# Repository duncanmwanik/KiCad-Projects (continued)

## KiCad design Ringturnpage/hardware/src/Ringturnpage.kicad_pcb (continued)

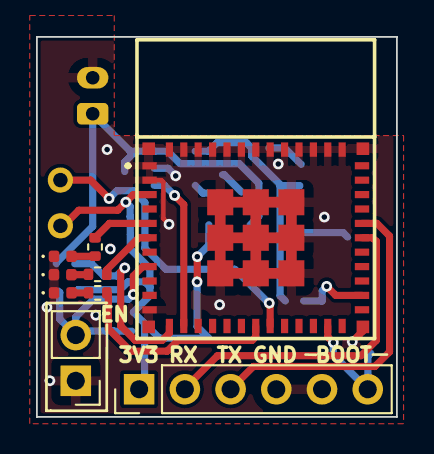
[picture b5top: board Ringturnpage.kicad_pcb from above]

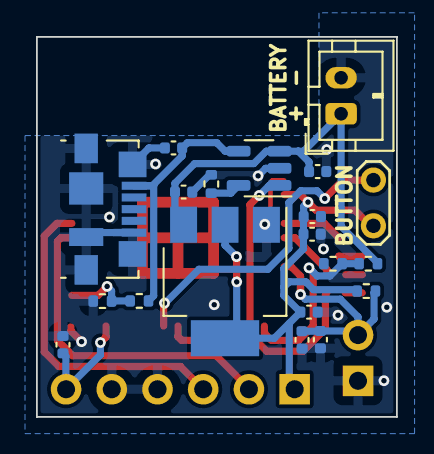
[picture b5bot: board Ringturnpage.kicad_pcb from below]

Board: 2 copper layers, 20.0 x 21.1 mm, 29 parts (20 on the bottom side), 19 nets.

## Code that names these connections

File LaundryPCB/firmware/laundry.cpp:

// ******* WASHING MACHINE CONTROLLER using WIFI
// Notifying control software about material left in the box not yet implemented
#include <Arduino.h>
#include <WiFi.h>
#include <HTTPClient.h>

const char* ssid = "WIFI_NAME";
const char* password = "WIFI_PASS";

const int START = 4;
const int STOP = 5;

// we use the solenoid taps rate of flow for each material and time
// to know what amount to dispense into the washing machine
const int WATER = 13;
const int HOT_WATER = 12;
const int BLEACH = 16;
const int POWDER = 14;
const int SOFTENER = 15;
const int BUZZER = 18;
const int WASHER = 18;
const int DRYER = 18;

// we use 
const int SENSOR_WATER = 2;
const int SENSOR_POWDER = 2;
const int SENSOR_BLEACH = 2;
const int SENSOR_SOFTENER = 2;

bool available = true;
bool start = false;

const char* get_order = "http://IP_ADDRESS_CONTROL_SOFTWARE/order";
const char* get_water = "http://IP_ADDRESS_CONTROL_SOFTWARE/water";
const char* get_hot_water = "http://IP_ADDRESS_CONTROL_SOFTWARE/hotwater";
const char* get_powder = "http://IP_ADDRESS_CONTROL_SOFTWARE/powder";
const char* get_bleach = "http://IP_ADDRESS_CONTROL_SOFTWARE/bleach";
const char* get_softener_size = "http://IP_ADDRESS_CONTROL_SOFTWARE/softener";
const char* get_start = "http://IP_ADDRESS_CONTROL_SOFTWARE/start";

String order = "none";
String hot_water_size;
String water_size;
String powder_size;
String bleach_size;
String softener_size;
String hot_water_size;
String start_str;

void setup() {

  pinMode(START, INPUT_PULLUP);
  pinMode(STOP, INPUT_PULLUP);
  pinMode(WATER, OUTPUT);
  pinMode(HOT_WATER, OUTPUT);
  pinMode(POWDER, OUTPUT);
  pinMode(BLEACH, OUTPUT);
  pinMode(SOFTENER, OUTPUT);
  pinMode(SENSOR_WATER, INPUT);
  pinMode(SENSOR_POWDER, INPUT);
  pinMode(SENSOR_BLEACH, INPUT);
  pinMode(SENSOR_SOFTENER, INPUT);

  WiFi.begin(ssid, password);
  while(WiFi.status() != WL_CONNECTED) { // turn LED on to show board is connected to WIFI
    delay(500);
    digitalWrite(GPIO_NUM_2, HIGH);
  }
}

void loop() {
  if(WiFi.status()== WL_CONNECTED){
    // if there is no order in progress
    if(order == "none"){
      order = httpGETRequest(get_order);
      hot_water_size = httpGETRequest(get_hot_water);
      water_size = httpGETRequest(get_water);
      powder_size = httpGETRequest(get_powder);
      bleach_size = httpGETRequest(get_bleach);
      softener_size = httpGETRequest(get_softener_size);
      
      // convert material values to int since these are time delay values
      int hot_water_value = hot_water_size.toInt();
      int water_value = water_size.toInt();
      int powder_value = powder_size.toInt();
      int bleach_value = bleach_size.toInt();
      int softener_value= softener_size.toInt();

      // if order is not empty, release material to the machine
      if(order != ""){
        // if the material value is 0, then that material won't be released
        // turn on each solenoid tap for the specified time period
        if(hot_water_value != 0){
          digitalWrite(HOT_WATER, HIGH);
          delay(hot_water_value);
          digitalWrite(HOT_WATER, LOW);
        }
        if(water_value != 0){
          digitalWrite(WATER, HIGH);
          delay(water_value);
          digitalWrite(WATER, LOW);
        }
        if(powder_value != 0){
          digitalWrite(POWDER, HIGH);
          delay(powder_value);
          digitalWrite(POWDER, LOW);
        }
        if(bleach_value != 0){
          digitalWrite(BLEACH, HIGH);
          delay(bleach_value);
          digitalWrite(BLEACH, LOW);
        }
        if(softener_value != 0){
          digitalWrite(SOFTENER, HIGH);
          delay(softener_value);
          digitalWrite(SOFTENER, LOW);
        }

      }
    }
    // if there is an order already in progress
    else{
      // get status value from control software
      start_str = httpGETRequest(get_start);
      // if START control button has been pressed
      if(digitalRead(START)){
        start_str = "1";
      }
      // if STOP control button has been pressed
      if(digitalRead(STOP)){
        start_str = "0";
      }
      // if 1, start washing process
      if(start_str=="1"){

        // DO WASHING PROCESS CODE

      }
      // if 0, stop washing process
      else if(start_str == "0"){
        
        // STOP WASHING PROCESS CODE

      }
      // if 2, cancel the order
      else if(start_str == "2"){

        order = "none";

      }

    }

  }
  else{ // flash LED on and off to show board has not connected to WIFI
    digitalWrite(GPIO_NUM_2, HIGH);
    delay(300);
    digitalWrite(GPIO_NUM_2, HIGH);
  }

}

String httpGETRequest(const char* serverName) {
  WiFiClient client;
  HTTPClient http;
    
  // Your Domain name with URL path or IP address with path
  http.begin(client, serverName);
  
  // Send HTTP POST request
  int httpResponseCode = http.GET();
  
  String payload = "--"; 
  
  if (httpResponseCode>0) {
    Serial.print("HTTP Response code: ");
    Serial.println(httpResponseCode);
    payload = http.getString();
  }
  else {
    Serial.print("Error code: ");
    Serial.println(httpResponseCode);
  }
  // Free resources
  http.end();

  return payload;
}

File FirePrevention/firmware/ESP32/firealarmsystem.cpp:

// ******* FIRE PREVENTION AND ALARM SYSTEM
#include <Arduino.h>
#include <WiFi.h>
#include <ESP_Mail_Client.h>
#include <HTTPClient.h>
#include <Firebase_ESP_Client.h>
#include "DHT.h"
#define DHTPIN 34 // Digital pin connected to the DHT sensor
#define DHTTYPE DHT22

//Provide the token generation process info.
#include "addons/TokenHelper.h"
//Provide the RTDB payload printing info and other helper functions.
#include "addons/RTDBHelper.h"

// Insert Firebase project API Key
#define API_KEY "FIREBASE_PROJECT_API_KEY"

// Insert RTDB URLefine the RTDB URL 
#define DATABASE_URL "FIREBASE_DATABASE_URL" 

// For the email service
#define SMTP_HOST "smtp.gmail.com"
#define SMTP_PORT 465
// The sign in credentials 
#define AUTHOR_EMAIL "mynamesgmail.com"
#define AUTHOR_PASSWORD "my_email_password"

// Recipient's email
#define RECIPIENT_EMAIL "receiveremail@gmail.com"

// The SMTP Session object used for Email sending 
SMTPSession smtp;

// Callback function to get the Email sending status 
void smtpCallback(SMTP_Status status);

//Define Firebase Data object
FirebaseData fbdo;

FirebaseAuth auth;
FirebaseConfig config;

bool signupOK = false;

// Temperature sensor instance
DHT dht(DHTPIN, DHTTYPE);

const char* ssid = "WIFI_NAME";
const char* password = "WIFI_PASS";

const int ALARM = 12;
const int GAS = 33;
const int FLAME = 32;

int counter = 0;  
static bool hasWifi = false;

//////////////
// Network //
////////////

static void InitWifi()
{
  Serial.println("Connecting...");
  WiFi.begin(ssid, password);
  while (WiFi.status() != WL_CONNECTED) {
    delay(500);
    Serial.print(".");
  }
  hasWifi = true;
  Serial.println("WiFi connected");
  Serial.println("IP address: ");
  Serial.println(WiFi.localIP());
}

void setup()
{
  Serial.begin(115200);
  pinMode(FLAME, INPUT);
  pinMode(GAS, INPUT);
  Serial.println("ESP32 Device");
  Serial.println("Initializing...");

    // Assign the api key (required) 
  config.api_key = API_KEY;

  // Assign the RTDB URL (required) 
  config.database_url = DATABASE_URL;

  // Sign up 
  if (Firebase.signUp(&config, &auth, "", "")){
    Serial.println("ok");
    signupOK = true;
  }
  else{
    Serial.printf("%s\n", config.signer.signupError.message.c_str());
  }

  // Assign the callback function for the long running token generation task 
  config.token_status_callback = tokenStatusCallback; //see addons/TokenHelper.h
  
  Firebase.begin(&config, &auth);
  Firebase.reconnectWiFi(true);
  
  dht.begin();

  // Initialize the WiFi module
  Serial.println(" > WiFi");
  hasWifi = false;
  InitWifi();
  if (!hasWifi)
  {
    return;
  }

  smtp.callback(smtpCallback);

  // Declare the session config data 
  ESP_Mail_Session session;

  // Set the session config 
  session.server.host_name = SMTP_HOST;
  session.server.port = SMTP_PORT;
  session.login.email = AUTHOR_EMAIL;
  session.login.password = AUTHOR_PASSWORD;
  session.login.user_domain = "";

  // Declare the message class 
  SMTP_Message message;

    // Set email parameters
    message.sender.name = "ESP_FIRE";
    message.sender.email = AUTHOR_EMAIL;
    message.subject = "FIRE DETECTED";
    message.addRecipient("Somebody", RECIPIENT_EMAIL);

}

//////////////
//Send Data//
////////////

void loop(){
  if (WiFi.status() == WL_CONNECTED) { //if we are connected
    counter = 0; //reset counter
    Serial.println("Wifi is still connected with IP: "); 
    Serial.println(WiFi.localIP());   //inform user about his IP address
  }else if (WiFi.status() != WL_CONNECTED) { //if we lost connection, retry
    WiFi.begin(ssid);      
  }
  while (WiFi.status() != WL_CONNECTED) { //during lost connection, print dots
    delay(500);
    Serial.print(".");
    counter++;
    if(counter>=60){ //30 seconds timeout - reset board
    ESP.restart();
    }
  }

  // Reading temperature, flame and gas values
  float t = dht.readTemperature();
  int f = analogRead(FLAME);
  int g = analogRead(GAS);
  
  // if connection and signup is successful, post sensor values 
  if (Firebase.ready() && signupOK){
    Firebase.RTDB.setFloat(&fbdo, "data/temp", t);
    Firebase.RTDB.setInt(&fbdo, "data/flame", f);
    Firebase.RTDB.setInt(&fbdo, "data/gas", g);
  }

  // if flame or gas or high temperatures is detected, activete fire alarm status
  if(f<1000 || g>1000 || t>100){
    // if connection and signup is successful, change alarm status to active(1)  
    if (Firebase.ready() && signupOK){
        Firebase.RTDB.setInt(&fbdo, "data/alarm", 1);
    }

    //Send the email
    String textMsg = "Fire has been detected. Do something asap! ";
    message.text.content = textMsg.c_str();
    message.text.charSet = "us-ascii";
    message.text.transfer_encoding = Content_Transfer_Encoding::enc_7bit;
    if (!MailClient.sendMail(&smtp, &message))
      Serial.println("Error sending Email, " + smtp.errorReason());

    digitalWrite (ALARM, HIGH); //sound alarm for 10 seconds
    delay(10000);
    digitalWrite (ALARM, LOW); //stop alarm

  }
  else{
    // if connection and signup is successful, change alarm status to inactive(0)
    // if fire is not detected anymore
    if (Firebase.ready() && signupOK){
        Firebase.RTDB.setInt(&fbdo, "data/alarm", 0);
    }
  }

}

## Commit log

2022-12-29 first add
